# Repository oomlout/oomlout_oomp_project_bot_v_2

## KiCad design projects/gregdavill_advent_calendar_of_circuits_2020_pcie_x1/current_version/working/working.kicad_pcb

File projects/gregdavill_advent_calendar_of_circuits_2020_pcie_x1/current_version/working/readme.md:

# advent_calendar_of_circuits_2020
 
## summary 
* id: gregdavill_advent_calendar_of_circuits_2020_pcie_x1
* user: gregdavill
* name: advent_calendar_of_circuits_2020
* board: pcie_x1
* repo: https://github.com/gregdavill/advent-calendar-of-circuits-2020
* src_file_repo_kicad_pcb: pcie_x1/kicad-src/pcie_x1.kicad_pcb
* src_file_repo_kicad_pcb_link: https://github.com/gregdavill/advent-calendar-of-circuits-2020/tree/main/pcie_x1/kicad-src/pcie_x1.kicad_pcb
* src_file_repo_kicad_sch: pcie_x1/kicad-src/pcie_x1.kicad_sch
* src_file_repo_kicad_sch_link: https://github.com/gregdavill/advent-calendar-of-circuits-2020/tree/main/pcie_x1/kicad-src/pcie_x1.kicad_sch

* src_file_repo_sch: 
* src_file_repo_sch_link: https://github.com/gregdavill/advent-calendar-of-circuits-2020/tree/main/
* full details link: https://github.com/oomlout/oomlout_oomp_project_bot_v_2/tree/main/projects/gregdavill_advent_calendar_of_circuits_2020_pcie_x1/current_version/working

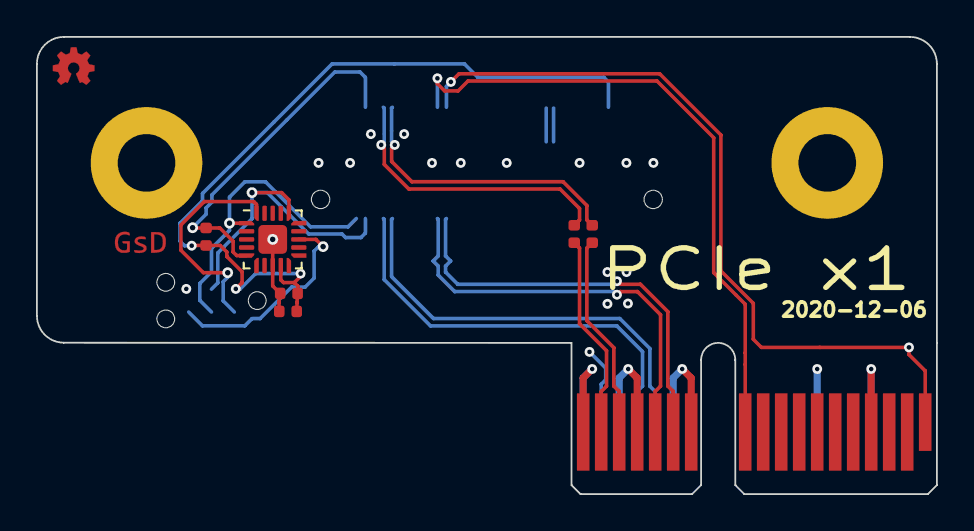
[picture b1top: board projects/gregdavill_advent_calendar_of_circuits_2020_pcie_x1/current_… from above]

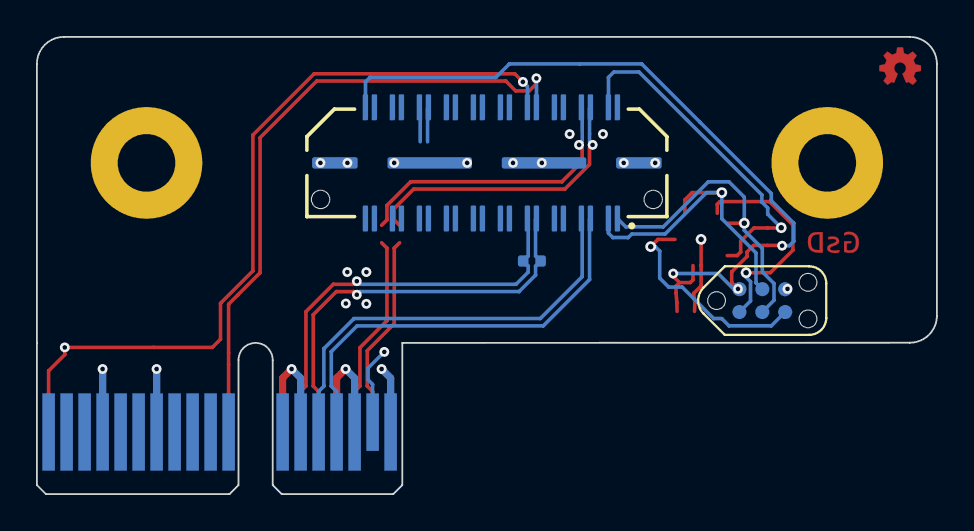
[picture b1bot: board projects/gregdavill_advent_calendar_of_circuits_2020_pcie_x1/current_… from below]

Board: 4 copper layers, 50.0 x 25.4 mm, 10 parts (4 on the bottom side), 17 nets.

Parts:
C1, C6, C9: 0.1uF; C_0402_1005Metric
C10: 1uF; C_0402_1005Metric
CN1: PCIE-x1; BUS_PCIexpress_x1
J1: SYZYGY-TXR-4; SYZYGY-TXR-POD
J3: TagConnect; TC2030-NL_SMALL
R1: 100R; R_0402_1005Metric
R15: 10K; R_0402_1005Metric
U2: ATtiny44A-MMH; QFN-20-1EP_3x3mm_P0.45mm_EP1.6x1.6mm

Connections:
+3V3: C9.1, C10.1, J1.40 (+3.3V), J3.2, R15.1, U2.9 (VCC)
/PER0_N: C6.2, CN1.A17 (PERn0)
/PER0_P: C1.2, CN1.A16 (PERp0)
/PERST#: CN1.A11 (PERST#), J1.14 (S0)
/PET0_N: CN1.B15 (PETn0), J1.5 (RX0P)
/PET0_P: CN1.B14 (PETp0), J1.7 (RX0N)
/PRSNT#: CN1.A1 (PRSNT1#), CN1.B17 (PRSNT3#), J1.16 (S1)
/Peripheral MCU/MISO: J3.1, U2.20 (PA5)
/Peripheral MCU/~RESET: J3.5, U2.13 (~RESET~/PB3)
/REFCLK_N: CN1.A14 (REFCLK-), J1.13 (REFCLKP), R1.1
/REFCLK_P: CN1.A13 (REFCLK+), J1.15 (REFCLKN), R1.2
/RGA: J1.4 (R_GA), R15.2, U2.5 (AREF/PA0)
/SCL: J1.1 (SCL), J3.3, U2.1 (PA4)
/SDA: J1.3 (SDA), J3.4, U2.16 (PA6)
/_PER0_N: C6.1, J1.6 (TX0P)
/_PER0_P: C1.1, J1.8 (TX0N)
GND: C9.2, C10.2, CN1.A4 (GND), CN1.A12 (GND), CN1.A15 (GND), CN1.A18 (GND), CN1.B4 (GND), CN1.B7 (GND), CN1.B13 (GND), CN1.B16 (GND), CN1.B18 (GND), J1.41 (GND), J3.6, U2.8 (GND), U2.21 (GND)

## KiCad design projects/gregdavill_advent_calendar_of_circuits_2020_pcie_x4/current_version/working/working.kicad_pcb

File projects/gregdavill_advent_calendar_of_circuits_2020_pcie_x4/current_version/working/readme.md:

# advent_calendar_of_circuits_2020
 
## summary 
* id: gregdavill_advent_calendar_of_circuits_2020_pcie_x4
* user: gregdavill
* name: advent_calendar_of_circuits_2020
* board: pcie_x4
* repo: https://github.com/gregdavill/advent-calendar-of-circuits-2020
* src_file_repo_kicad_pcb: pcie_x4/kicad-src/pcie_x4.kicad_pcb
* src_file_repo_kicad_pcb_link: https://github.com/gregdavill/advent-calendar-of-circuits-2020/tree/main/pcie_x4/kicad-src/pcie_x4.kicad_pcb
* src_file_repo_kicad_sch: pcie_x4/kicad-src/pcie_x4.kicad_sch
* src_file_repo_kicad_sch_link: https://github.com/gregdavill/advent-calendar-of-circuits-2020/tree/main/pcie_x4/kicad-src/pcie_x4.kicad_sch

* src_file_repo_sch: 
* src_file_repo_sch_link: https://github.com/gregdavill/advent-calendar-of-circuits-2020/tree/main/
* full details link: https://github.com/oomlout/oomlout_oomp_project_bot_v_2/tree/main/projects/gregdavill_advent_calendar_of_circuits_2020_pcie_x4/current_version/working

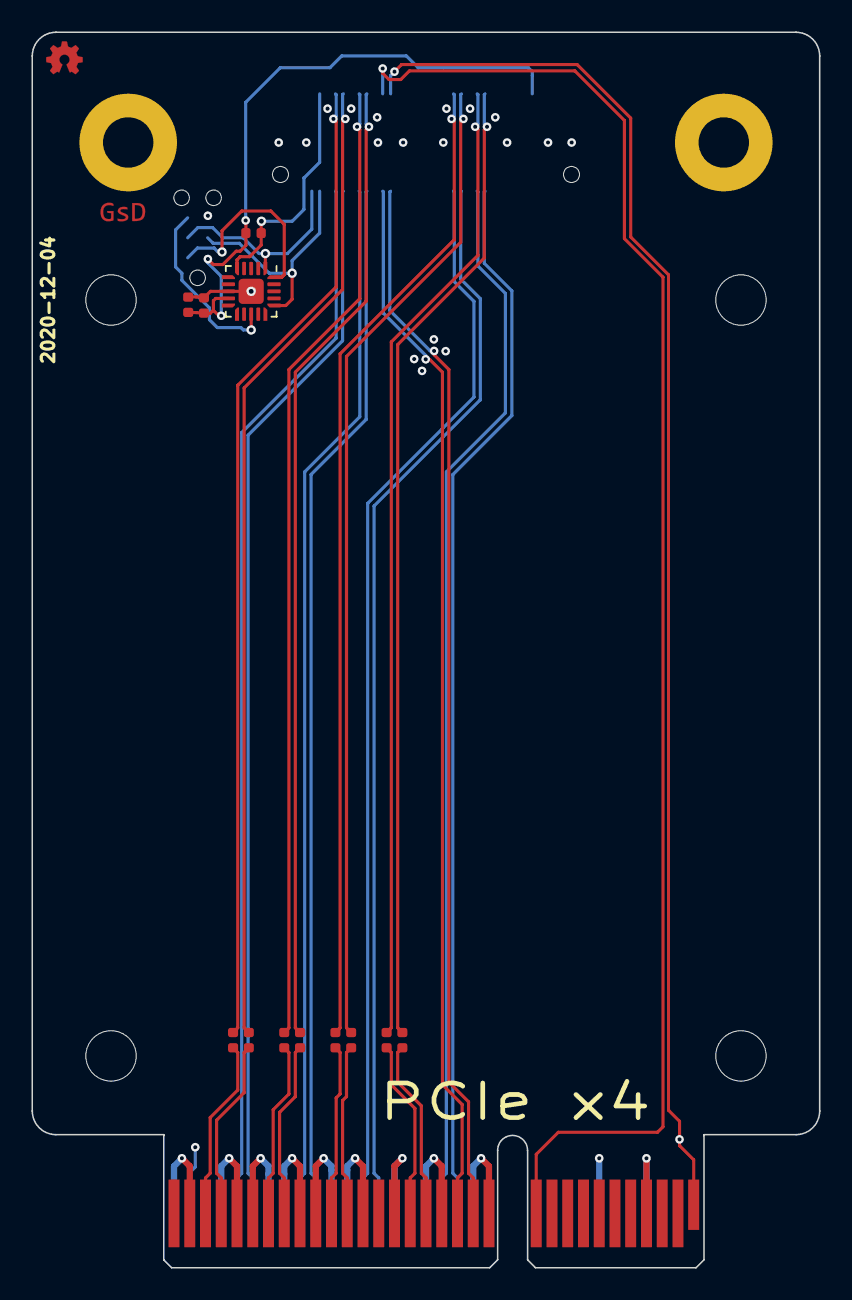
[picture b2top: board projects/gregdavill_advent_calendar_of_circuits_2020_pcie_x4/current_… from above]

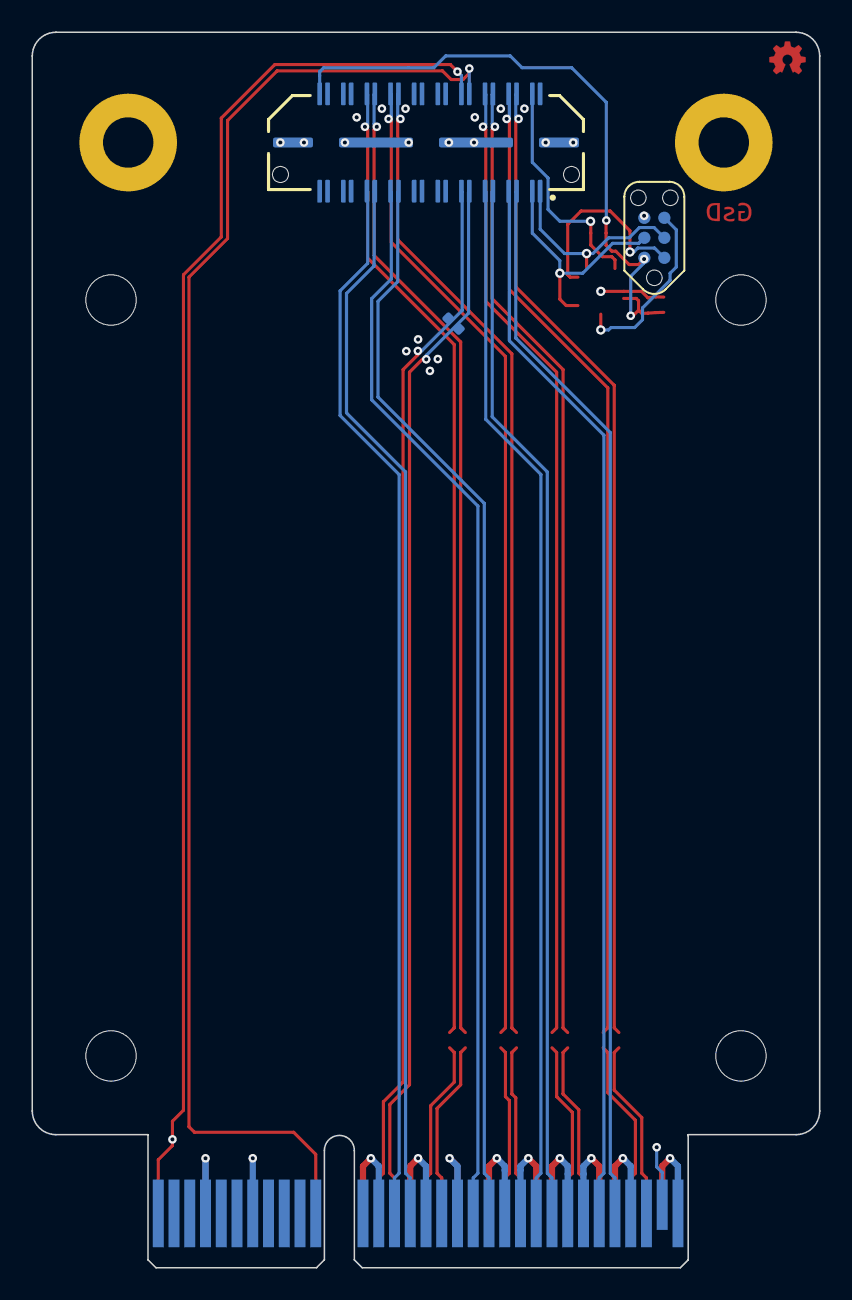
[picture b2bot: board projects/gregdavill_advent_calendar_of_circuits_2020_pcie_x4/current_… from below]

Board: 4 copper layers, 50.0 x 78.5 mm, 20 parts (4 on the bottom side), 35 nets.

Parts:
C1, C2, C3, C4, C6, C7, C8, C9, C11: 0.1uF; C_0402_1005Metric
C10: 1uF; C_0402_1005Metric
CN1: PCI-EXPRESS-EDGE-FINGER; BUS_PCIexpress_x4
H1, H2, H3, H4: MountingHole; MountingHole_3.2mm_M3
J1: SYZYGY-TXR-4; SYZYGY-TXR-POD
J3: TagConnect; TC2030-NL_SMALL
R1: 100R; R_0402_1005Metric
R15: 10K; R_0402_1005Metric
U2: ATtiny44A-MMH; QFN-20-1EP_3x3mm_P0.45mm_EP1.6x1.6mm

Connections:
+3V3: C9.1, C10.1, J1.40 (+3.3V), J3.2, R15.1, U2.9 (VCC)
/PER0_N: C6.2, CN1.A17 (PERn0)
/PER0_P: C1.2, CN1.A16 (PERp0)
/PER1_N: C7.2, CN1.A22 (PERn1)
/PER1_P: C2.2, CN1.A21 (PERp1)
/PER2_N: C8.2, CN1.A26 (PERn2)
/PER2_P: C3.2, CN1.A25 (PERp2)
/PER3_N: C11.2, CN1.A30 (PERn3)
/PER3_P: C4.2, CN1.A29 (PERp3)
/PERST#: CN1.A11 (PERST#), J1.14 (S0)
/PET0_N: CN1.B15 (PETn0), J1.29 (RX2P)
/PET0_P: CN1.B14 (PETp0), J1.31 (RX2N)
/PET1_N: CN1.B20 (PETn1), J1.25 (RX3P)
/PET1_P: CN1.B19 (PETp1), J1.27 (RX3N)
/PET2_N: CN1.B24 (PETn2), J1.9 (RX1P)
/PET2_P: CN1.B23 (PETp2), J1.11 (RX1N)
/PET3_N: CN1.B28 (PETn3), J1.5 (RX0P)
/PET3_P: CN1.B27 (PETp3), J1.7 (RX0N)
/PRSNT#: CN1.A1 (PRSNT1#), CN1.B31 (PRSNT#), J1.16 (S1)
/Peripheral MCU/MISO: J3.1, U2.20 (PA5)
/Peripheral MCU/~RESET: J3.5, U2.13 (~RESET~/PB3)
/REFCLK_N: CN1.A14 (REFCLK-), J1.13 (REFCLKP), R1.1
/REFCLK_P: CN1.A13 (REFCLK+), J1.15 (REFCLKN), R1.2
/RGA: J1.4 (R_GA), R15.2, U2.5 (AREF/PA0)
/SCL: J1.1 (SCL), J3.3, U2.1 (PA4)
/SDA: J1.3 (SDA), J3.4, U2.16 (PA6)
/_PER0_N: C6.1, J1.30 (TX2P)
/_PER0_P: C1.1, J1.32 (TX2N)
/_PER1_N: C7.1, J1.26 (TX3P)
/_PER1_P: C2.1, J1.28 (TX3N)
/_PER2_N: C8.1, J1.10 (TX1P)
/_PER2_P: C3.1, J1.12 (TX1N)
/_PER3_N: C11.1, J1.6 (TX0P)
/_PER3_P: C4.1, J1.8 (TX0N)
GND: C9.2, C10.2, CN1.A4 (GND), CN1.A12 (GND), CN1.A15 (GND), CN1.A18 (GND), CN1.A20 (GND), CN1.A23 (GND), CN1.A24 (GND), CN1.A27 (GND), CN1.A28 (GND), CN1.A31 (GND), CN1.B4 (GND), CN1.B7 (GND), CN1.B13 (GND), CN1.B16 (GND), CN1.B18 (GND), CN1.B21 (GND), CN1.B22 (GND), CN1.B25 (GND), CN1.B26 (GND), CN1.B29 (GND), CN1.B32 (GND), J1.41 (GND), J3.6, U2.8 (GND), U2.21 (GND)

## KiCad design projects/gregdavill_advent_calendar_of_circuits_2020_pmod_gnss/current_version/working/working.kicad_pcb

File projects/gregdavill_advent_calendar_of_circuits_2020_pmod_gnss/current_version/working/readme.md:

# advent_calendar_of_circuits_2020
 
## summary 
* id: gregdavill_advent_calendar_of_circuits_2020_pmod_gnss
* user: gregdavill
* name: advent_calendar_of_circuits_2020
* board: pmod_gnss
* repo: https://github.com/gregdavill/advent-calendar-of-circuits-2020
* src_file_repo_kicad_pcb: pmod-gnss/kicad-src/pmod-gnss.kicad_pcb
* src_file_repo_kicad_pcb_link: https://github.com/gregdavill/advent-calendar-of-circuits-2020/tree/main/pmod-gnss/kicad-src/pmod-gnss.kicad_pcb
* src_file_repo_kicad_sch: pmod-gnss/kicad-src/pmod-gnss.kicad_sch
* src_file_repo_kicad_sch_link: https://github.com/gregdavill/advent-calendar-of-circuits-2020/tree/main/pmod-gnss/kicad-src/pmod-gnss.kicad_sch

* src_file_repo_sch: 
* src_file_repo_sch_link: https://github.com/gregdavill/advent-calendar-of-circuits-2020/tree/main/
* full details link: https://github.com/oomlout/oomlout_oomp_project_bot_v_2/tree/main/projects/gregdavill_advent_calendar_of_circuits_2020_pmod_gnss/current_version/working

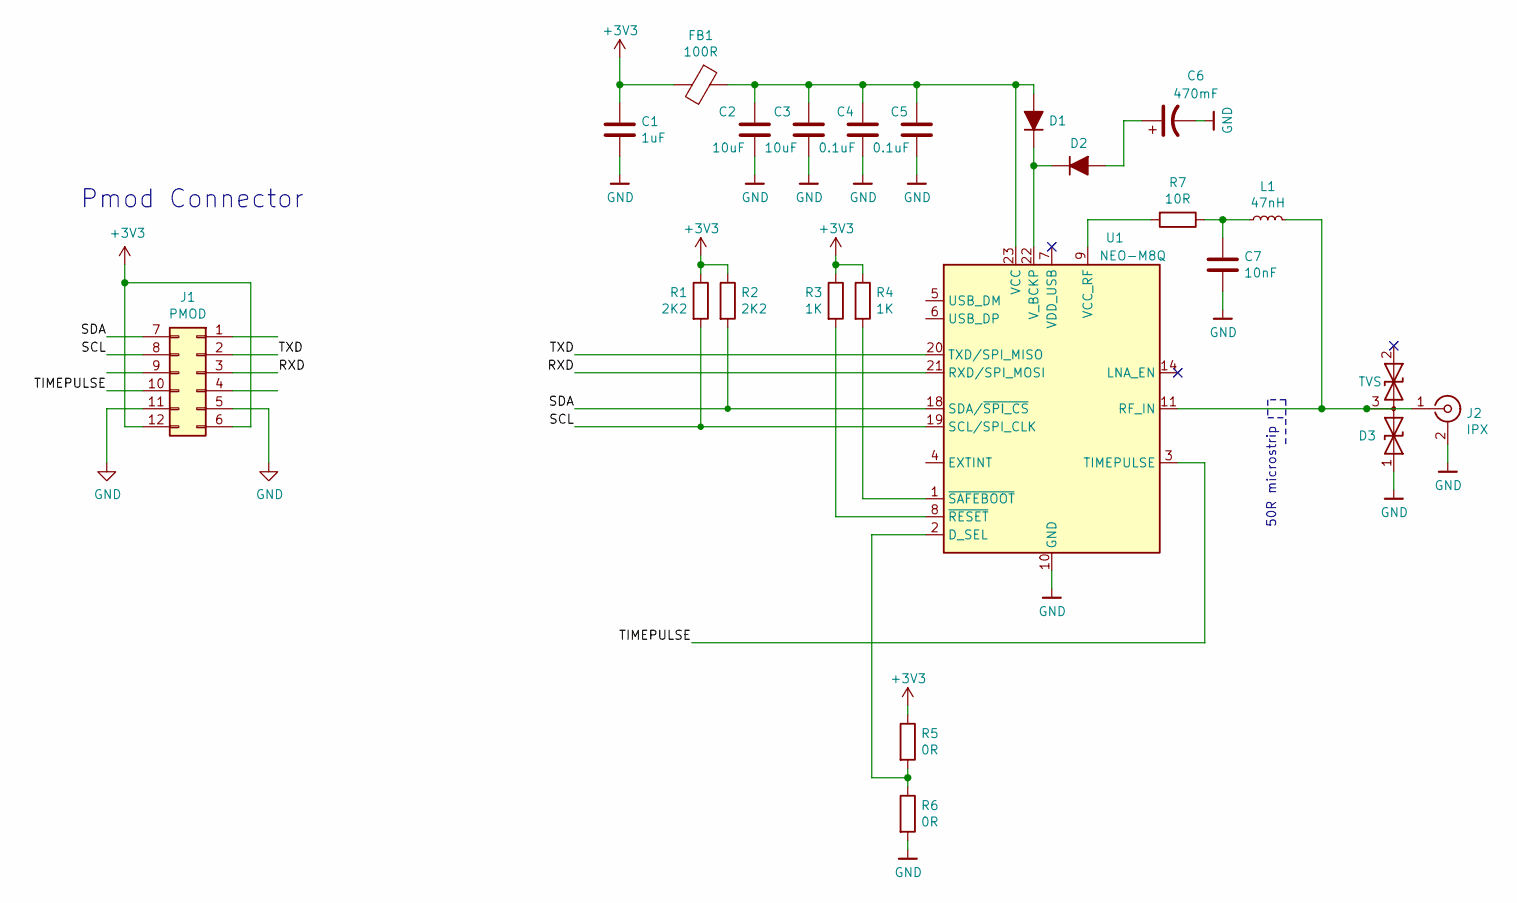
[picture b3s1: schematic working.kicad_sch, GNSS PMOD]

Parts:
C1: 1uF; C_0402_1005Metric
C2, C3: 10uF; C_0603_1608Metric
C4, C5: 0.1uF; C_0402_1005Metric
C6: 470mF; BatteryHolder_Keystone_2998_1x6.8mm
C7: 10nF; C_0402_1005Metric
D1, D2: D_ALT; D_SOD-123F
D3: TVS; SOT-323_SC-70
FB1: 100R; L_0603_1608Metric
J1: PMOD; PinHeader_2x06_P2.54mm_Horizontal
J2: IPX; SMA_Amphenol_132289_EdgeMount
L1: 47nH; L_0402_1005Metric
R1, R2: 2K2; R_0402_1005Metric
R3, R4: 1K; R_0402_1005Metric
R5, R6: 0R; R_0402_1005Metric
R7: 10R; R_0402_1005Metric
U1: NEO-M8Q; ublox_NEO

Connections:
+3V3: C1.1, FB1.2, J1.6, J1.12, R1.1, R2.1, R3.1, R4.1, R5.1
/RXD: J1.3, U1.21 (RXD/SPI_MOSI)
/SCL: J1.8, R1.2, U1.19 (SCL/SPI_CLK)
/SDA: J1.7, R2.2, U1.18 (SDA/~SPI_CS)
/TIMEPULSE: J1.10, U1.3 (TIMEPULSE)
/TXD: J1.2, U1.20 (TXD/SPI_MISO)
GND: C1.2, C2.2, C3.2, C4.2, C5.2, C6.2, C7.2, D3.1 (A1), J1.5, J1.11, J2.2 (Ext), R6.2, U1.10 (GND), U1.12 (GND), U1.13 (GND), U1.24 (GND)
unnamed: C2.1, C3.1, C4.1, C5.1, D1.2 (A), FB1.1, U1.23 (VCC)
unnamed: C6.1, D2.2 (A)
unnamed: C7.1, L1.1, R7.1
unnamed: D1.1 (K), D2.1 (K), U1.22 (V_BCKP)
unnamed: D3.3 (common), J2.1 (In), L1.2, U1.11 (RF_IN)
unnamed: R3.2, U1.8 (~RESET)
unnamed: R4.2, U1.1 (~SAFEBOOT)
unnamed: R5.2, R6.1, U1.2 (D_SEL)
unnamed: R7.2, U1.9 (VCC_RF)
no_connect_23: D3.2 (A2)
no_connect_24: U1.14 (LNA_EN)
no_connect_25: U1.15 (RESERVED)
no_connect_26: U1.16 (RESERVED)
no_connect_27: U1.17 (RESERVED)
no_connect_28: U1.7 (VDD_USB)

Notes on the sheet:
Pmod Connector
50R microstrip

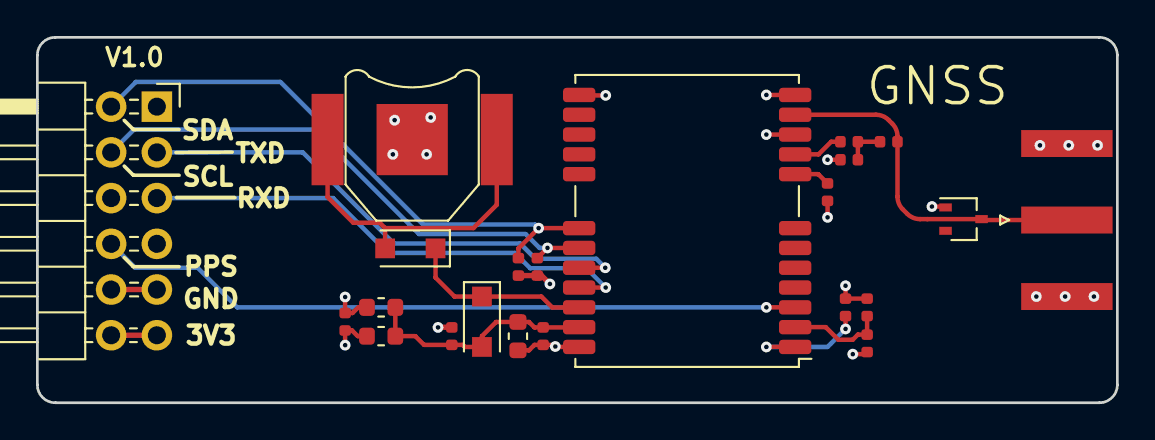
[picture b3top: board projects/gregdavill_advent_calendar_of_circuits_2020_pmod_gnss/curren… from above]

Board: 4 copper layers, 60.0 x 20.3 mm, 22 parts (0 on the bottom side), 16 nets.

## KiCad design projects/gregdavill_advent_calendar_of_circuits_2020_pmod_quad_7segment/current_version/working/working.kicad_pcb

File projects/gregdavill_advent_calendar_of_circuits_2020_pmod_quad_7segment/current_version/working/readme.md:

# advent_calendar_of_circuits_2020
 
## summary 
* id: gregdavill_advent_calendar_of_circuits_2020_pmod_quad_7segment
* user: gregdavill
* name: advent_calendar_of_circuits_2020
* board: pmod_quad_7segment
* repo: https://github.com/gregdavill/advent-calendar-of-circuits-2020
* src_file_repo_kicad_pcb: pmod-quad-7segment/kicad-src/pmod-quad-7segment.kicad_pcb
* src_file_repo_kicad_pcb_link: https://github.com/gregdavill/advent-calendar-of-circuits-2020/tree/main/pmod-quad-7segment/kicad-src/pmod-quad-7segment.kicad_pcb
* src_file_repo_kicad_sch: pmod-quad-7segment/kicad-src/pmod-quad-7segment.kicad_sch
* src_file_repo_kicad_sch_link: https://github.com/gregdavill/advent-calendar-of-circuits-2020/tree/main/pmod-quad-7segment/kicad-src/pmod-quad-7segment.kicad_sch

* src_file_repo_sch: 
* src_file_repo_sch_link: https://github.com/gregdavill/advent-calendar-of-circuits-2020/tree/main/
* full details link: https://github.com/oomlout/oomlout_oomp_project_bot_v_2/tree/main/projects/gregdavill_advent_calendar_of_circuits_2020_pmod_quad_7segment/current_version/working

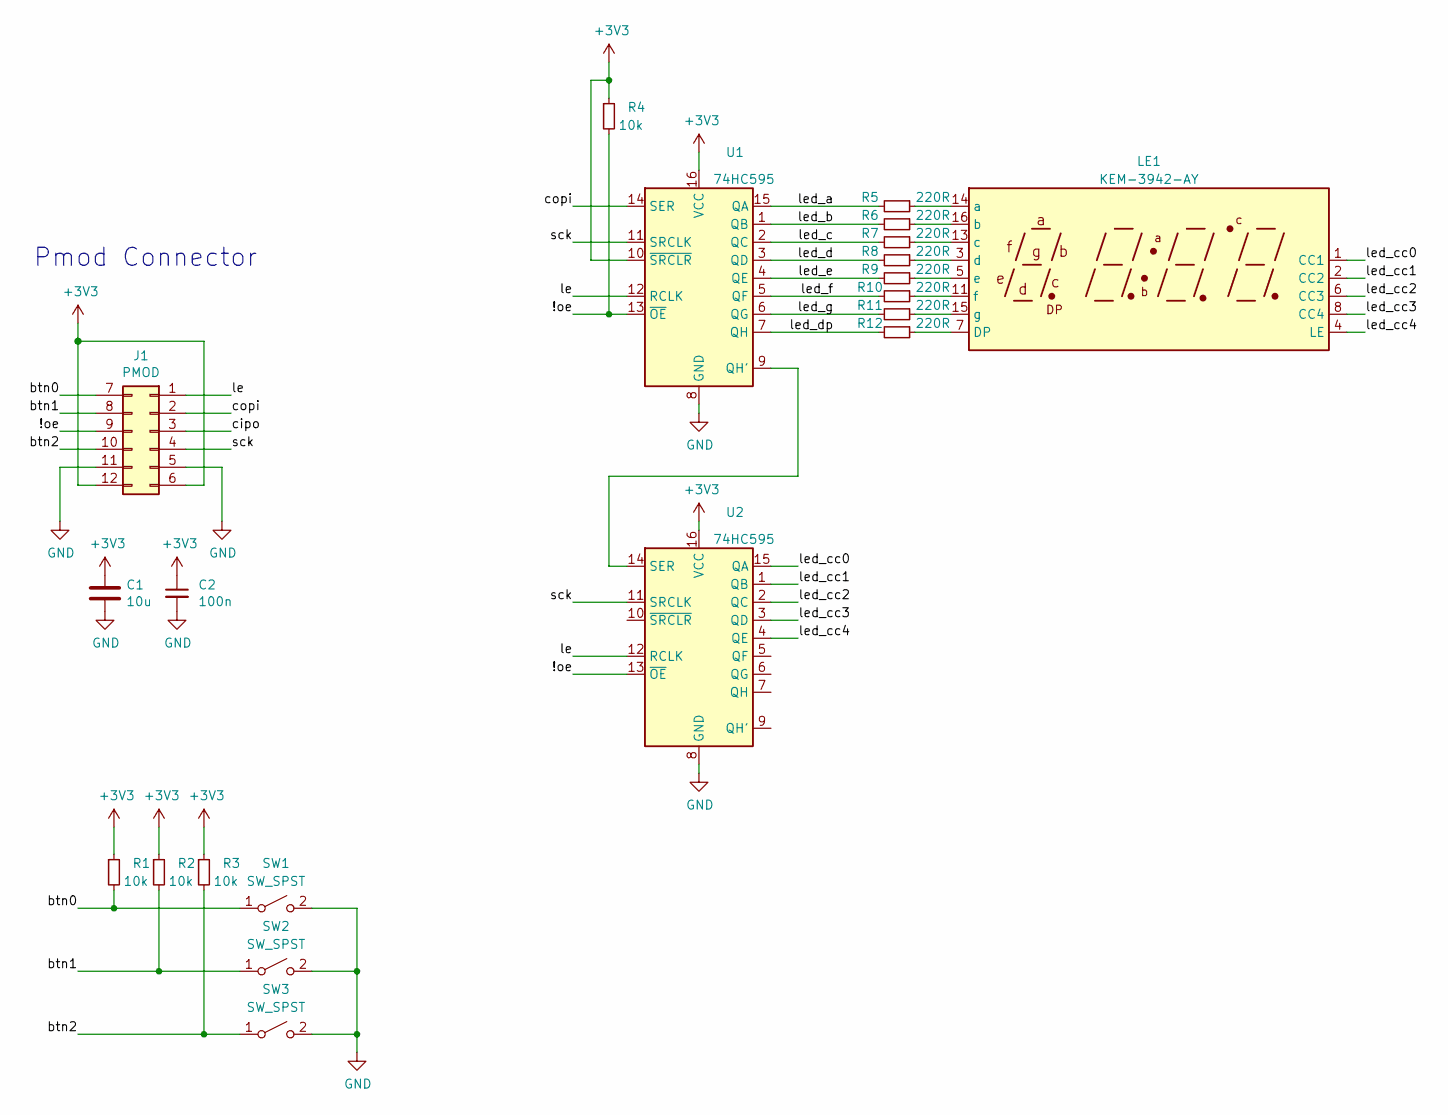
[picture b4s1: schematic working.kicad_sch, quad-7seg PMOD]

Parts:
C1: 10u; C_0603_1608Metric
C2: 100n; C_0402_1005Metric
J1: PMOD; PinHeader_2x06_P2.54mm_Horizontal
LE1: KEM-3942-AY; kem-3942-ay
R1, R2, R3, R4: 10k; R_0402_1005Metric
R5, R6, R7, R8, R9, R10, R11, R12: 220R; R_0402_1005Metric
SW1, SW2, SW3: SW_SPST; SW_SPST_PTS810
U1, U2: 74HC595; TSSOP-16_4.4x5mm_P0.65mm

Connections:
+3V3: C1.1, C2.1, J1.6, J1.12, R1.1, R2.1, R3.1, R4.1, U1.10 (~SRCLR), U1.16 (VCC), U2.16 (VCC)
/!oe: J1.9, R4.2, U1.13 (~OE), U2.13 (~OE)
/btn0: J1.7, R1.2, SW1.1 (A)
/btn1: J1.8, R2.2, SW2.1 (A)
/btn2: J1.10, R3.2, SW3.1 (A)
/cipo: J1.3
/copi: J1.2, U1.14 (SER)
/le: J1.1, U1.12 (RCLK), U2.12 (RCLK)
/led_a: R5.2, U1.15 (QA)
/led_b: R6.2, U1.1 (QB)
/led_c: R7.2, U1.2 (QC)
/led_cc0: LE1.1 (CC1), U2.15 (QA)
/led_cc1: LE1.2 (CC2), U2.1 (QB)
/led_cc2: LE1.6 (CC3), U2.2 (QC)
/led_cc3: LE1.8 (CC4), U2.3 (QD)
/led_cc4: LE1.4 (LE), U2.4 (QE)
/led_d: R8.2, U1.3 (QD)
/led_dp: R12.2, U1.7 (QH)
/led_e: R9.2, U1.4 (QE)
/led_f: R10.2, U1.5 (QF)
/led_g: R11.2, U1.6 (QG)
/sck: J1.4, U1.11 (SRCLK), U2.11 (SRCLK)
GND: C1.2, C2.2, J1.5, J1.11, SW1.2 (B), SW2.2 (B), SW3.2 (B), U1.8 (GND), U2.8 (GND)
unnamed: LE1.3 (d), R8.1
unnamed: LE1.5 (e), R9.1
unnamed: LE1.7 (DP), R12.1
unnamed: LE1.11 (f), R10.1
unnamed: LE1.13 (c), R7.1
unnamed: LE1.14 (a), R5.1
unnamed: LE1.15 (g), R11.1
unnamed: LE1.16 (b), R6.1
unnamed: U1.9 (QH'), U2.14 (SER)

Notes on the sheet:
Pmod Connector

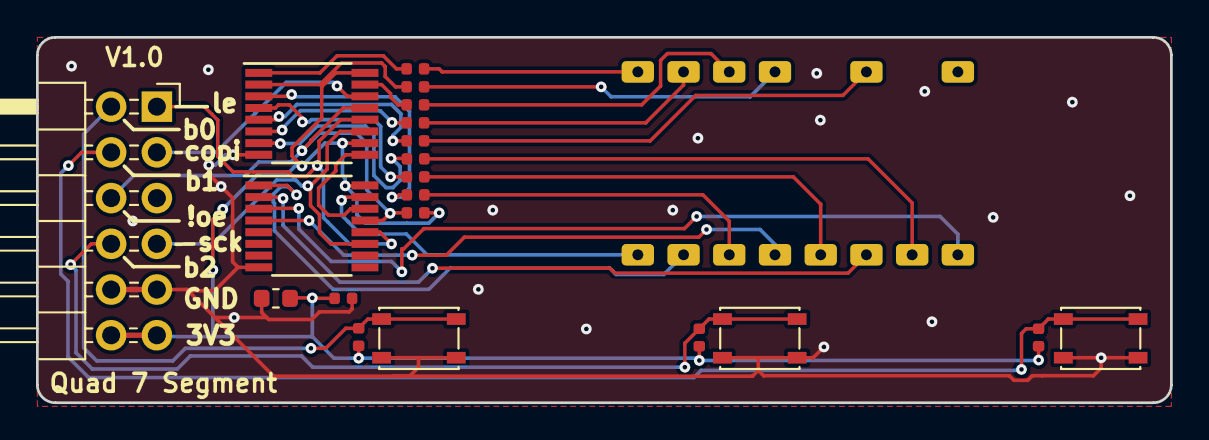
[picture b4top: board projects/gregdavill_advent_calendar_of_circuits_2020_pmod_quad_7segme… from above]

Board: 2 copper layers, 63.0 x 20.3 mm, 21 parts (0 on the bottom side), 31 nets.

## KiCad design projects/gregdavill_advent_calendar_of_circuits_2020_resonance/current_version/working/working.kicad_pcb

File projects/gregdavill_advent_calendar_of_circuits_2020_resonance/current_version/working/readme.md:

# advent_calendar_of_circuits_2020
 
## summary 
* id: gregdavill_advent_calendar_of_circuits_2020_resonance
* user: gregdavill
* name: advent_calendar_of_circuits_2020
* board: resonance
* repo: https://github.com/gregdavill/advent-calendar-of-circuits-2020
* src_file_repo_kicad_pcb: resonance/kicad-src/resonance.kicad_pcb
* src_file_repo_kicad_pcb_link: https://github.com/gregdavill/advent-calendar-of-circuits-2020/tree/main/resonance/kicad-src/resonance.kicad_pcb
* src_file_repo_kicad_sch: resonance/kicad-src/connectors.kicad_sch
* src_file_repo_kicad_sch_link: https://github.com/gregdavill/advent-calendar-of-circuits-2020/tree/main/resonance/kicad-src/connectors.kicad_sch

* src_file_repo_sch: 
* src_file_repo_sch_link: https://github.com/gregdavill/advent-calendar-of-circuits-2020/tree/main/
* full details link: https://github.com/oomlout/oomlout_oomp_project_bot_v_2/tree/main/projects/gregdavill_advent_calendar_of_circuits_2020_resonance/current_version/working

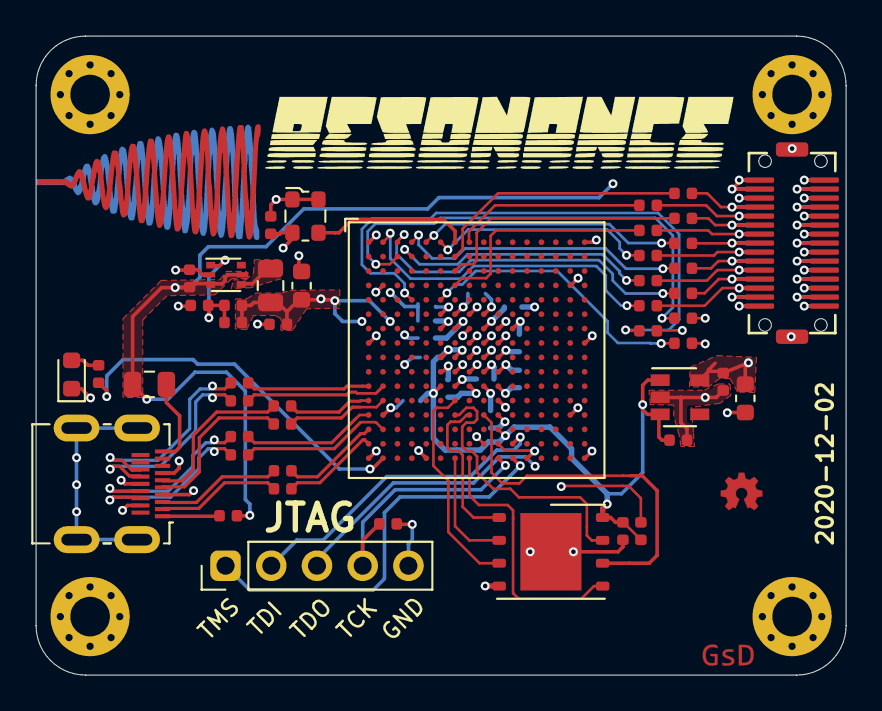
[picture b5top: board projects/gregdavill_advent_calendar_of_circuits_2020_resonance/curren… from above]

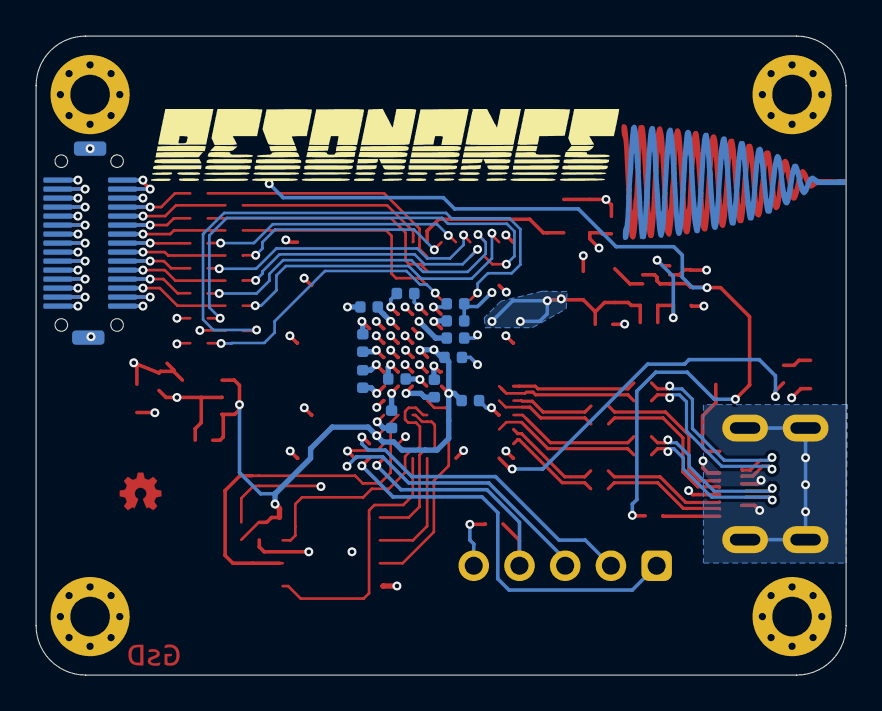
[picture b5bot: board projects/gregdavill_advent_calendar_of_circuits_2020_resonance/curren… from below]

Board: 4 copper layers, 45.0 x 35.5 mm, 66 parts (13 on the bottom side), 75 nets.

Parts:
C1, C2, C3, C4, C5, C6, C7, C8, C16, C17, C18, C19, C20, C21, C22, C23, C24, C25, C26, C27, C28, C29: 0.1uF; C_0402_1005Metric
C9, C10: 4.7uF; C_0402_1005Metric
C11, C14: 10uF; C_0603_1608Metric
C12, C15: 1uF; C_0402_1005Metric
C13: 6.8pF; C_0402_1005Metric
D1: YELLOW; LED_0603_1608Metric
F1: 50mA; Fuse_0805_2012Metric
H1, H4: ECG_VCM; MountingHole_2.2mm_M2_Pad_Via
H2, H3: MountingHole_Pad; MountingHole_2.2mm_M2_Pad_Via
J1: Conn_02x15_Top_Bottom_MountingPin; 10132797-035100LF
J2: Conn_02x15_Top_Bottom_MountingPin; 10132798-30
J3: HDMI_D_1.4; HDMI_Micro-D_Molex_46765-1x01
J4: Conn_01x05_Male; PinHeader_1x05_P2.54mm_Vertical
L1: 2.2uH; L_0805_2012Metric
LOGO1: Q_NMOS_GSD; gsd_logo_small
LOGO2: Logo_Open_Hardware_Small; oshw_small
R1: 84k5; R_0402_1005Metric
R2: 100k; R_0402_1005Metric
R3, R5, R19: 2k; R_0402_1005Metric
R4: 1k; R_0402_1005Metric
R6, R7, R8, R9, R10, R11, R12, R13, R14, R15, R16, R17, R18: 100R; R_0402_1005Metric
U1: W25Q32JVZP; WSON-8-1EP_6x5mm_P1.27mm_EP3.4x4.3mm
U2: ECP5U-12-CABGA256; BGA-256_14.0x14.0mm_Layout16x16_P0.8mm_Ball0.45mm_Pad0.32mm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
U3: TLV62569DRL; SOT-666
U4: AP2127K-2.5; SOT-23-5
X1: ECS-2520MV-xxx-xx; Oscillator_SMD_ECS_2520MV-xxx-xx-4Pin_2.5x2.0mm

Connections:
+1V1: C13.1, C14.1, C15.1, C22.1, C23.1, C24.1, C25.1, C26.1, C27.1, L1.2, R1.2, U2.G6 (VCC[6]), U2.G7 (VCC[6]), U2.G9 (VCC[6]), U2.L8 (VCC[6]), U2.L9 (VCC[6]), U2.L10 (VCC[6])
+2V5: C11.1, C12.1, C20.1, C21.1, U2.G11 (VCCAUX[2]), U2.L7 (VCCAUX[2]), U4.5 (VOUT)
+3V3: C10.1, C16.1, C17.1, C18.1, C19.1, C28.1, C29.1, J1.2, J2.2, R19.2, U1.8 (VCC), U2.F6 (VCCIO0[2]), U2.F7 (VCCIO0[2]), U2.J6 (VCCIO6[2]), U2.J7 (VCCIO6[2]), U2.L6 (VCCIO8), U2.P10 (CFG_1), U4.1 (VIN), U4.3 (EN), X1.1 (Tri-State), X1.4 (VDD)
+5V: C9.1, F1.1, J1.3, J2.3, R4.2, U3.3 (VIN), U3.5 (EN)
/Connectors/1V8: J1.1, J2.1
/Connectors/BAT+: J1.16, J1.17, J2.16, J2.17
/Connectors/ECG_N: J1.14, J2.14
/Connectors/ECG_P: J1.15, J2.15
/Connectors/ECG_VCM: J1.30, J2.30
/Connectors/GPIO1: J1.10, J2.10, R16.1
/Connectors/GPIO2: J1.22, J2.22, R9.1
/Connectors/GPIO3: J1.21, J2.21, R8.1
/Connectors/GPIO5: J1.11, J2.11, R17.1
/Connectors/LED_CLK: J1.8, J2.8
/Connectors/LED_DAT: J1.9, J2.9
/Connectors/MAX30101_INT: J1.5, J2.5
/Connectors/PMIC_GPIO: J1.20, J2.20, R7.1
/Connectors/PMIC_nEN: J1.19, J2.19, R6.1
/Connectors/SCL_1V8: J1.7, J2.7
/Connectors/SCL_3V3: J1.12, J2.12, R18.1
/Connectors/SDA_1V8: J1.6, J2.6
/Connectors/SDA_3V3: J1.28, J2.28, R15.1
/Connectors/SPI_CIPO: J1.25, J2.25, R12.1
/Connectors/SPI_COPI: J1.24, J2.24, R11.1
/Connectors/SPI_GPIO4: J1.27, J2.27, R14.1
/Connectors/SPI_SCK: J1.26, J2.26, R13.1
/Connectors/SPI_SS0: J1.23, J2.23, R10.1
/fpga/CFG_CLK: U1.6 (CLK), U2.N9 (CCLK/MCLK/SCK)
/fpga/CFG_CS: U1.1 (~CS), U2.N8 (PB15A/+/HOLDN/DI/BUSY/CSSPIN/CEN)
/fpga/CFG_IO0: U1.5 (DI(IO0)), U2.T8 (PB11B/-/D0/MOSI/IO0)
/fpga/CFG_IO1: U1.2 (DO(IO1)), U2.T7 (PB11A/+/D1/MISO/IO1)
/fpga/CFG_IO2: U1.3 (IO2), U2.M7 (PB9B/-/D2/IO2)
/fpga/CFG_IO3: U1.7 (IO3), U2.N7 (PB9A/+/D3/IO3)
/fpga/CK+: C8.1, U2.L2 (PL26B/-/PCLKC6_1/HS/LDQ32)
/fpga/CK-: C4.2, U2.L1 (PL26A/+/PCLKT6_1/HS/LDQ32)
/fpga/D0+: C7.1, U2.M2 (PL26D/-/PCLKC6_0/LDQ32)
/fpga/D0-: C3.2, U2.M1 (PL26C/+/PCLKT6_0/LDQ32)
/fpga/D1+: C6.1, U2.P2 (PL32B/-/HS/LDQSN32)
/fpga/D1-: C2.2, U2.N1 (PL32A/+/HS/LDQS32)
/fpga/D2+: C5.1, U2.R1 (PL35B/-/VREF1_6/HS/LDQ32)
/fpga/D2-: C1.2, U2.P1 (PL35A/+/HS/LDQ32)
/fpga/TCK: J4.4, R5.2, U2.T10 (TCK)
/fpga/TDI: J4.2, U2.R11 (TDI)
/fpga/TDO: J4.3, U2.M10 (TDO)
/fpga/TMS: J4.1, U2.T11 (TMS)
/fpga/_CK+: C8.2, J3.12 (CK+)
/fpga/_CK-: C4.1, J3.14 (CK-)
/fpga/_D0+: C7.2, J3.9 (D0+)
/fpga/_D0-: C3.1, J3.11 (D0-)
/fpga/_D1+: C6.2, J3.6 (D1+)
/fpga/_D1-: C2.1, J3.8 (D1-)
/fpga/_D2+: C5.2, J3.3 (D2+)
/fpga/_D2-: C1.1, J3.5 (D2-)
GND: C9.2, C10.2, C11.2, C12.2, C14.2, C15.2, C16.2, C17.2, C18.2, C19.2, C20.2, C21.2, C22.2, C23.2, C24.2, C25.2, C26.2, C27.2, C28.2, C29.2, D1.1 (K), J1.4, J1.13, J1.18, J1.29, J1.MP (MountPin), J2.4, J2.13, J2.18, J2.29, J2.MP (MountPin), J3.4 (D2S), J3.7 (D1S), J3.10 (D0S), J3.13 (CKS), J3.SH, J4.5, R2.1, R5.1, U1.4 (GND), U1.9 (EP), U2.A1 (GND[27]), U2.A16 (GND[27]), U2.D2 (GND[27]), U2.D15 (GND[27]), U2.F8 (GND[27]), U2.F9 (GND[27]), U2.G8 (GND[27]), U2.G10 (GND[27]), U2.H1 (GND[27]), U2.H8 (GND[27]), U2.H9 (GND[27]), U2.H10 (GND[27]), U2.H16 (GND[27]), U2.J8 (GND[27]), U2.J9 (GND[27]), U2.J10 (GND[27]), U2.K6 (GND[27]), U2.K7 (GND[27]), U2.K8 (GND[27]), U2.K9 (GND[27]), U2.K10 (GND[27]), U2.N2 (GND[27]), U2.N10 (CFG_0), U2.N15 (GND[27]), U2.R10 (CFG_2), U2.T1 (GND[27]), U2.T5 (GND[27]), U2.T12 (GND[27]), U2.T16 (GND[27]), U3.2 (GND), U4.2 (GND), X1.2 (GND)
unnamed: C13.2, R1.1, R2.2, U3.1 (FB)
unnamed: D1.2 (A), R3.2
unnamed: J3.1 (HPD/HEAC-), R4.1
unnamed: F1.2, J3.19 (+5V)
unnamed: L1.1, U3.4 (SW)
unnamed: U2.A7 (PT29A/+/PCLKT0_0), X1.3 (OUT)
unnamed: R19.1, U2.R9 (PROGRAMN)
unnamed: R3.1, U2.T2 (PL38D/-/LDQ44)
_GPIO1: R16.2, U2.B3 (PT4B/-)
_GPIO2: R9.2, U2.D7 (PT24B/-/GR_PCLK0_0)
_GPIO3: R8.2, U2.C7 (PT27A/+/PCLKT0_1)
_GPIO5: R17.2, U2.E4 (PT9A/+)
_PMIC_GPIO: R7.2, U2.A8 (PT29B/-/PCLKC0_0)
_PMIC_nEN: R6.2, U2.B7 (PT27B/-/PCLKC0_1)
_SCL_3V3: R18.2, U2.E6 (PT20A/+)
_SDA_3V3: R15.2, U2.A2 (PT4A/+)
_SPI_CIPO: R12.2, U2.A4 (PT6B/-)
_SPI_COPI: R11.2, U2.A6 (PT18B/-)
_SPI_GPIO4: R14.2, U2.A3 (PT6A/+)
_SPI_SCK: R13.2, U2.B4 (PT11B/-)
_SPI_SS0: R10.2, U2.A5 (PT18A/+)

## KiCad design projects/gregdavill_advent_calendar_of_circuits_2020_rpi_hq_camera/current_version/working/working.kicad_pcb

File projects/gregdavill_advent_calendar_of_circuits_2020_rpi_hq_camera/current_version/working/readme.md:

# advent_calendar_of_circuits_2020
 
## summary 
* id: gregdavill_advent_calendar_of_circuits_2020_rpi_hq_camera
* user: gregdavill
* name: advent_calendar_of_circuits_2020
* board: rpi_hq_camera
* repo: https://github.com/gregdavill/advent-calendar-of-circuits-2020
* src_file_repo_kicad_pcb: rpi-hq-camera/kicad-src/rpi-hq-camera.kicad_pcb
* src_file_repo_kicad_pcb_link: https://github.com/gregdavill/advent-calendar-of-circuits-2020/tree/main/rpi-hq-camera/kicad-src/rpi-hq-camera.kicad_pcb
* src_file_repo_kicad_sch: rpi-hq-camera/kicad-src/p-mcu.kicad_sch
* src_file_repo_kicad_sch_link: https://github.com/gregdavill/advent-calendar-of-circuits-2020/tree/main/rpi-hq-camera/kicad-src/p-mcu.kicad_sch

* src_file_repo_sch: 
* src_file_repo_sch_link: https://github.com/gregdavill/advent-calendar-of-circuits-2020/tree/main/
* full details link: https://github.com/oomlout/oomlout_oomp_project_bot_v_2/tree/main/projects/gregdavill_advent_calendar_of_circuits_2020_rpi_hq_camera/current_version/working

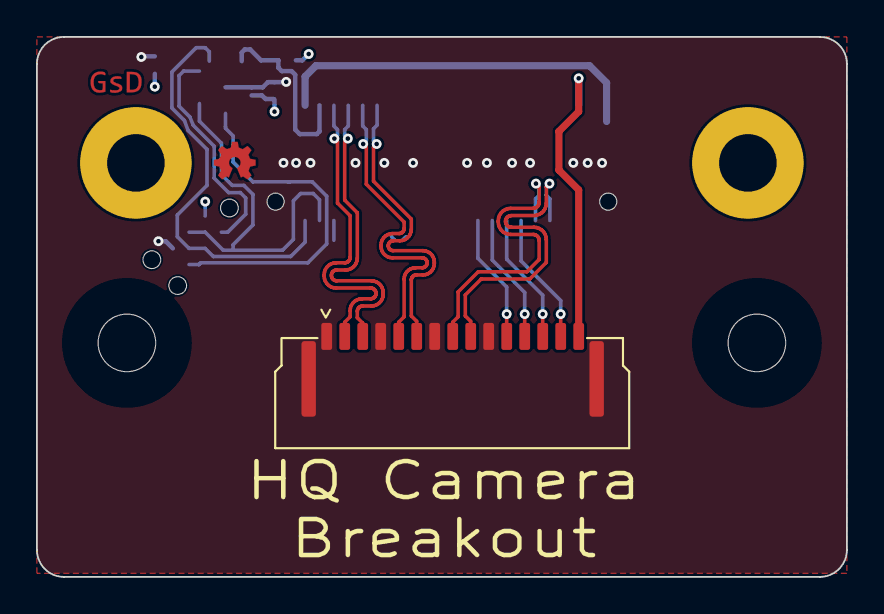
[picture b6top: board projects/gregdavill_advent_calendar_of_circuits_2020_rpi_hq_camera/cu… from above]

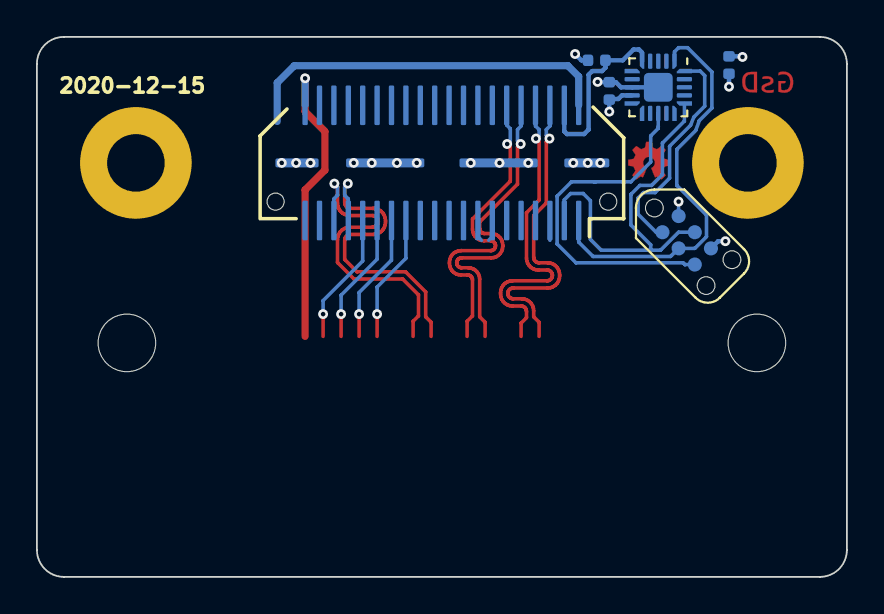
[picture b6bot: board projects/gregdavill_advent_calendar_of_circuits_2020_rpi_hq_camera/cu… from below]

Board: 4 copper layers, 45.0 x 30.0 mm, 9 parts (6 on the bottom side), 17 nets.

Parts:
C9: 0.1uF; C_0402_1005Metric
C10: 1uF; C_0402_1005Metric
H1, H2: MountingHole; MountingHole_3.2mm_M3_DIN965
J1: SYZYGY-STD; SYZYGY-STD-POD
J3: TagConnect; TC2030-NL_SMALL
J7: Conn_01x15_MountingPin; FCI_SFW15R-1STE1LF_1x15-1MP_P1.00mm_Horizontal
R15: 10K; R_0402_1005Metric
U2: ATtiny44A-MMH; QFN-20-1EP_3x3mm_P0.45mm_EP1.6x1.6mm

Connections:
+3V3: C9.1, C10.1, J1.40 (+3.3V), J3.2, J7.15, R15.1, U2.9 (VCC)
/CAM_SCL: J1.29 (S24), J7.13
/CAM_SDA: J1.31 (S26), J7.14
/CSI_CLK_N: J1.33 (P2C_CLKP), J7.8
/CSI_CLK_P: J1.35 (P2C_CLKN), J7.9
/CSI_D0_N: J1.6 (S1_D1P), J7.2
/CSI_D0_P: J1.8 (S3_D1N), J7.3
/CSI_D1_N: J1.10 (S5_D3P), J7.5
/CSI_D1_P: J1.12 (S7_D3N), J7.6
/ENABLE: J1.25 (S20), J7.11
/GPIO: J1.27 (S22), J7.12
/Peripheral MCU/MISO: J3.1, U2.20 (PA5)
/Peripheral MCU/~RESET: J3.5, U2.13 (~RESET~/PB3)
/RGA: J1.4 (R_GA), R15.2, U2.5 (AREF/PA0)
/SCL: J1.1 (SCL), J3.3, U2.1 (PA4)
/SDA: J1.3 (SDA), J3.4, U2.16 (PA6)
GND: C9.2, C10.2, J1.41 (GND), J3.6, J7.1, J7.4, J7.7, J7.10, J7.MP (MountPin), U2.8 (GND), U2.21 (GND)

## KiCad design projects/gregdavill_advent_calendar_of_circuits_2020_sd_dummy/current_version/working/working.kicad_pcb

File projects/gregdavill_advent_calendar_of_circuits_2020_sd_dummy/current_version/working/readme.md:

# advent_calendar_of_circuits_2020
 
## summary 
* id: gregdavill_advent_calendar_of_circuits_2020_sd_dummy
* user: gregdavill
* name: advent_calendar_of_circuits_2020
* board: sd_dummy
* repo: https://github.com/gregdavill/advent-calendar-of-circuits-2020
* src_file_repo_kicad_pcb: pmod-sd-dummy/kicad-src/sd-dummy.kicad_pcb
* src_file_repo_kicad_pcb_link: https://github.com/gregdavill/advent-calendar-of-circuits-2020/tree/main/pmod-sd-dummy/kicad-src/sd-dummy.kicad_pcb
* src_file_repo_kicad_sch: pmod-sd-dummy/kicad-src/sd-dummy.kicad_sch
* src_file_repo_kicad_sch_link: https://github.com/gregdavill/advent-calendar-of-circuits-2020/tree/main/pmod-sd-dummy/kicad-src/sd-dummy.kicad_sch

* src_file_repo_sch: 
* src_file_repo_sch_link: https://github.com/gregdavill/advent-calendar-of-circuits-2020/tree/main/
* full details link: https://github.com/oomlout/oomlout_oomp_project_bot_v_2/tree/main/projects/gregdavill_advent_calendar_of_circuits_2020_sd_dummy/current_version/working

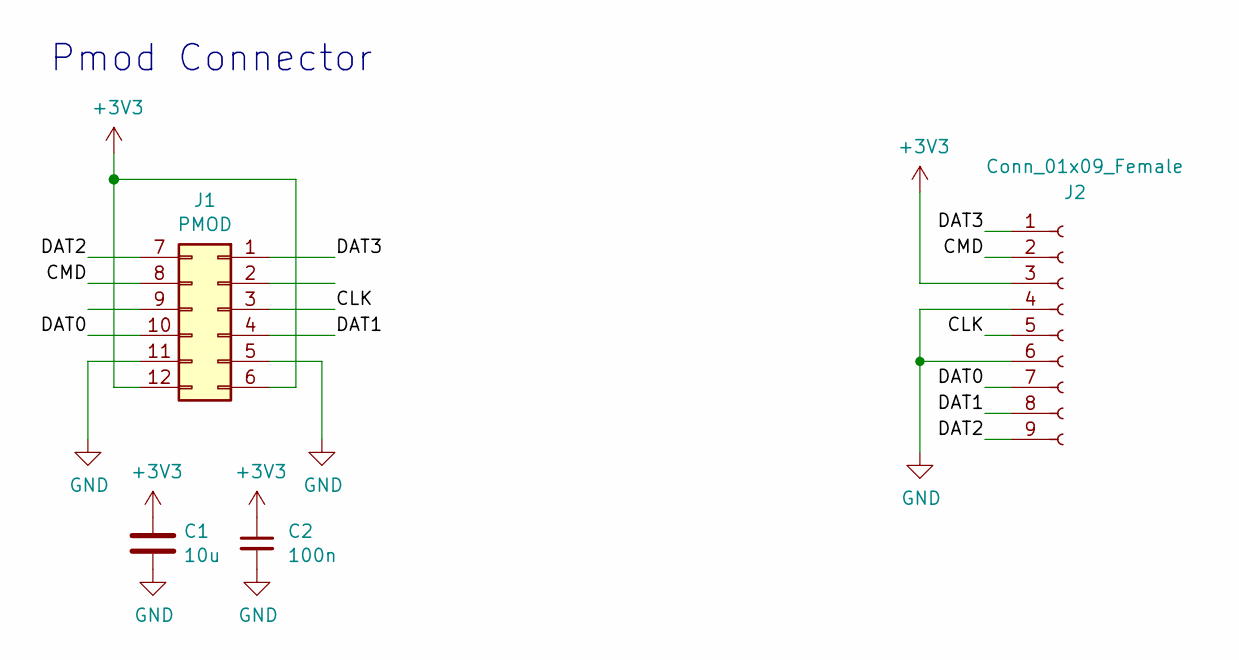
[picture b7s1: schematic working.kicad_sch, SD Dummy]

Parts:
C1: 10u; C_0603_1608Metric
C2: 100n; C_0402_1005Metric
J1: PMOD; PinHeader_2x06_P2.54mm_Horizontal
J2: Conn_01x09_Female; SD_PCB

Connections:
+3V3: C1.1, C2.1, J1.6, J1.12, J2.3
/CLK: J1.3, J2.5
/CMD: J1.8, J2.2
/DAT0: J1.10, J2.7
/DAT1: J1.4, J2.8
/DAT2: J1.7, J2.9
/DAT3: J1.1, J2.1
GND: C1.2, C2.2, J1.5, J1.11, J2.4, J2.6

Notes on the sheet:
Pmod Connector

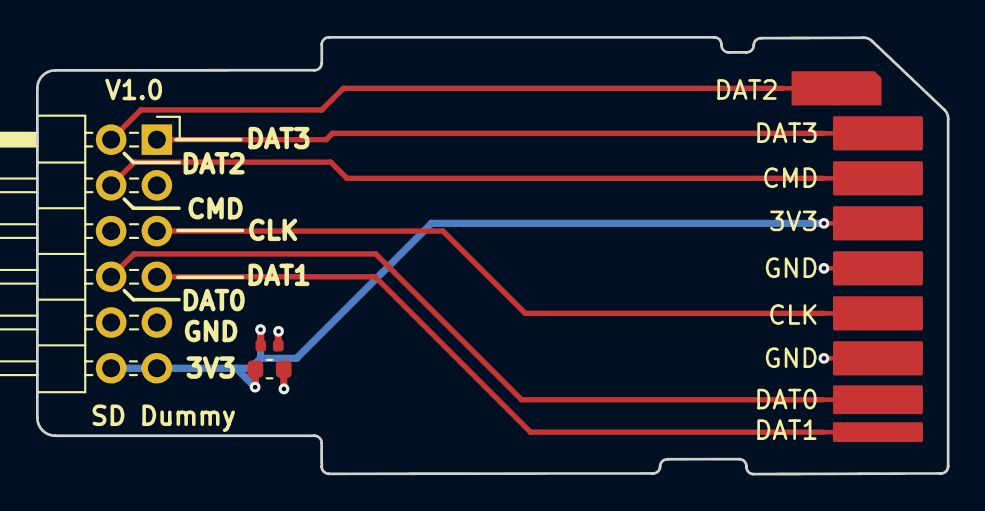
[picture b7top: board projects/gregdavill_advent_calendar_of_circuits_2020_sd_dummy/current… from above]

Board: 4 copper layers, 50.6 x 24.3 mm, 4 parts (0 on the bottom side), 8 nets.
